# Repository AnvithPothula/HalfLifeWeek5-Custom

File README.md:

# HalfLifeWeek5-Custom

For Week 5 I designed a smart chess clock. It has two OLED screens side by side like a normal chess clock, 5 MX keys, a piezo buzzer, and it runs on 3 AA batteries. After a game, it can connect to Wi-Fi and export the game, with how much time each player had on every move, to a Lichess study.

**3D Model / Final PCB Render:**

**Schematic:**

**Board Layout & Routing:**

Combined Layout:

Front Copper Layer:

Back Copper Layer:

**What it is and how it works:**

Each player has a big key on their side. When you finish your move, you press your key, which stops your clock and starts your opponent's. The 3 keys in the middle are -, Start and +.

The clock has:

- 9 time control presets
- A custom mode where White and Black can have different times
- Increment or delay mode
- A double beep when you drop under 10 seconds, and a long beep when your time runs out
- Tenths of a second on the screen when you have under 20 seconds
- Saving of the last 5 games
- A page where you replay the moves and export the game to a Lichess study
- Deep sleep after 5 minutes of not being used

This is what the screens show during a game (the player whose turn it is gets a highlighted bar at the top):

These are the parts:

* **Waveshare ESP32-S3-Zero:** This is the brain of the board and runs the clocks, saves the games, and connects to Wi-Fi for the export.
* **2 OLED screens:** There is one for each player and shows all of the informaion.
* **4 solder jumpers:** Some of these screens have their pins in the order VCC, GND, SCL, SDA and others have GND, VDD, SCK, SDA. The jumpers let you pick the right order for your screens, so both versions work on the same PCB.
* **5 MX keys:** Each key connects a pin to GND, and the ESP32's pull-up resistors keep the pin HIGH until it's pressed.
* **1N5819 diode:** The 3 AA batteries go through this into the 5V pin. When USB is plugged in, it stops USB power from flowing back into the batteries.
* **2 10k resistors:** These halve the battery voltage so the ESP32 can read the battery level.
* **10uF capacitor:** This smooths out the 5V power.
* **Piezo buzzer:** This makes the beeps.

To export a game, hold Start after the game ends. The clock connects to Wi-Fi and shows its IP address on the left screen. Open that address in a browser on the same Wi-Fi. The page builds the PGN with the clock time for every move, and the clock sends it to the Lichess study.

Note: I used Claude to help write the webpage/exporting part of the code.

**Why I made it:**

I play and coach chess a lot, so a chess clock is something I would actually use. Normal chess clocks don't save anything, so after an over-the-board game, there's no record of how much time each move took. To put it into a chess engine to analyze the game, we would have to notate the game, and then after the game manually enter the moves. With this clock, I can put the game into Lichess and see where I spent too much time. This was also my first project without a guide, where I made the schematic, PCB and firmware all on my own.

**How to assemble and flash the firmware:**

**1. How to assemble the board**

You need a soldering iron, solder, flux, tweezers, flush cutters, a multimeter, and double-sided tape.

First, set the screen jumpers. Look at the back of your screens and check the pin labels. If the screen says VCC GND SCL SDA, bridge the middle pad of JP1 and JP3 to the 3V3 pad, and bridge the middle pad of JP2 and JP4 to the GND pad. If it says GND VDD SCK SDA, do the opposite.

To bridge a jumper, melt a little solder on the middle pad and drag it onto the pad you want.

Then solder from the flattest part to the tallest part:

1. **C1 (10uF capacitor):** Put a little solder on one pad, hold the capacitor with tweezers, and melt that pad to tack it down. Then solder the other end.
2. **R1, R2 (Resistors):** Bend the legs, push them through, solder and trim.
3. **D1 (Diode):** The grey stripe goes on the side with the bar on the silkscreen.
4. **U1 (ESP32-S3-Zero):** Line it up with the outline, with the USB-C port at the top edge. Tack one corner, then solder every edge pad and check for bridges.
5. **SW1–SW5 (MX keys):** Push each key in and then solder its 2 pins.
6. **J1, J2 (screens):** Push each screen's header pins through its 4 holes. Solder one pin, check that the screen is straight, then solder the rest.
7. **Keycaps:** Press them on.

The battery holder and piezo are the only parts with wires. They go on the back of the board:

1. Stick the battery holder to the back with double-sided tape. On J3 (labelled Battery), solder the red wire to the square pad (BAT+) and the black wire to the round pad (GND).
2. Stick the piezo disc to the back with tape or hot glue. Solder its wires to the 2 pads of J4 (labelled Piezo).

Before plugging in, use the multimeter in continuity mode to check that 5V, 3V3 and GND are not shorted, and that each jumper's middle pad only connects to one side.

**2. How to flash the firmware**

1. Install the Arduino IDE.
2. In the Boards Manager, install esp32 by Espressif Systems and select ESP32S3 Dev Module as the board.
3. Under the Tools menu, set USB CDC On Boot to Enabled so the Serial Monitor works over USB-C.
4. Install these libraries in the Library Manager:
   * Adafruit SSD1306
   * Adafruit GFX
   * ArduinoJson
5. Copy ChessClockArduino/secrets_example.h to ChessClockArduino/secrets.h and fill in your Wi-Fi name and password.
6. To export to Lichess, make a token with the study:write scope [here](https://lichess.org/account/oauth/token/create?scopes[]=study:write&description=Chess+Clock) and paste it into LICHESS_TOKEN in secrets.h. Then make a study on Lichess, and put its 8-character ID (from the study's URL) in DEFAULT_STUDY_ID at the top of ChessClockArduino.ino.
7. Open ChessClockArduino/ChessClockArduino.ino, plug the board in with a USB-C data cable, and click Upload. If it doesn't upload, hold the BOOT button on the ESP32-S3-Zero, tap RESET, release BOOT, and try again.

Both screens should show the time. Press Start, and White's clock should start counting down. secrets.h is in .gitignore, so your Wi-Fi password and token won't be uploaded to GitHub.

**BOM:**

The full bill of materials is in [BOM.csv](BOM.csv):

| Item | Qty | Supplier | Cost/item | Total cost | Link |
| --- | ---: | --- | ---: | ---: | --- |
| ESP32-S3-Zero (no headers) | 1 | AliExpress | $4.32 | $4.32 | [AliExpress](https://www.aliexpress.us/item/3256807949476561.html) |
| 0.96" OLED 128x64 I2C (SSD1306, white 2-pack) | 1 | AliExpress | $4.40 | $4.40 | [AliExpress](https://www.aliexpress.us/item/3256805954920554.html) |
| 27mm piezo with wires (10-pack) | 1 | AliExpress | $4.70 | $4.70 | [AliExpress](https://www.aliexpress.us/item/3256806921009045.html) |
| 3x AA battery holder with switch | 1 | AliExpress | $1.44 | $1.44 | [AliExpress](https://www.aliexpress.us/item/2255800794307346.html) |
| 1N5819 Schottky diode (50-pack) | 1 | AliExpress | $1.32 | $1.32 | [AliExpress](https://www.aliexpress.us/item/3256801365779334.html) |
| MX switches (10-pack, red) | 1 | AliExpress | $1.88 | $1.88 | [AliExpress](https://www.aliexpress.us/item/3256807066857216.html) |
| Keycaps (10-pack, red) | 1 | AliExpress | $2.32 | $2.32 | [AliExpress](https://www.aliexpress.us/item/3256807312571573.html) |
| 10k resistors (spare from Week 4) | 2 | — | $0.00 | $0.00 | — |
| 10uF 0805 capacitor (spare from Week 4) | 1 | — | $0.00 | $0.00 | — |
| PCB | 1 | JLCPCB | $4.00 | $4.00 | [JLCPCB](https://jlcpcb.com/) |
| Shipping (AliExpress Choice) | — | AliExpress | — | $0.00 | — |
| Shipping (JLCPCB Global Standard Direct Line) | — | JLCPCB | — | $3.78 (-$5 coupon) | — |
| Estimated sales tax (8.125% on AliExpress parts) | — | — | — | $1.66 | — |
| **Estimated total** |  |  |  | **$29.82** |  |

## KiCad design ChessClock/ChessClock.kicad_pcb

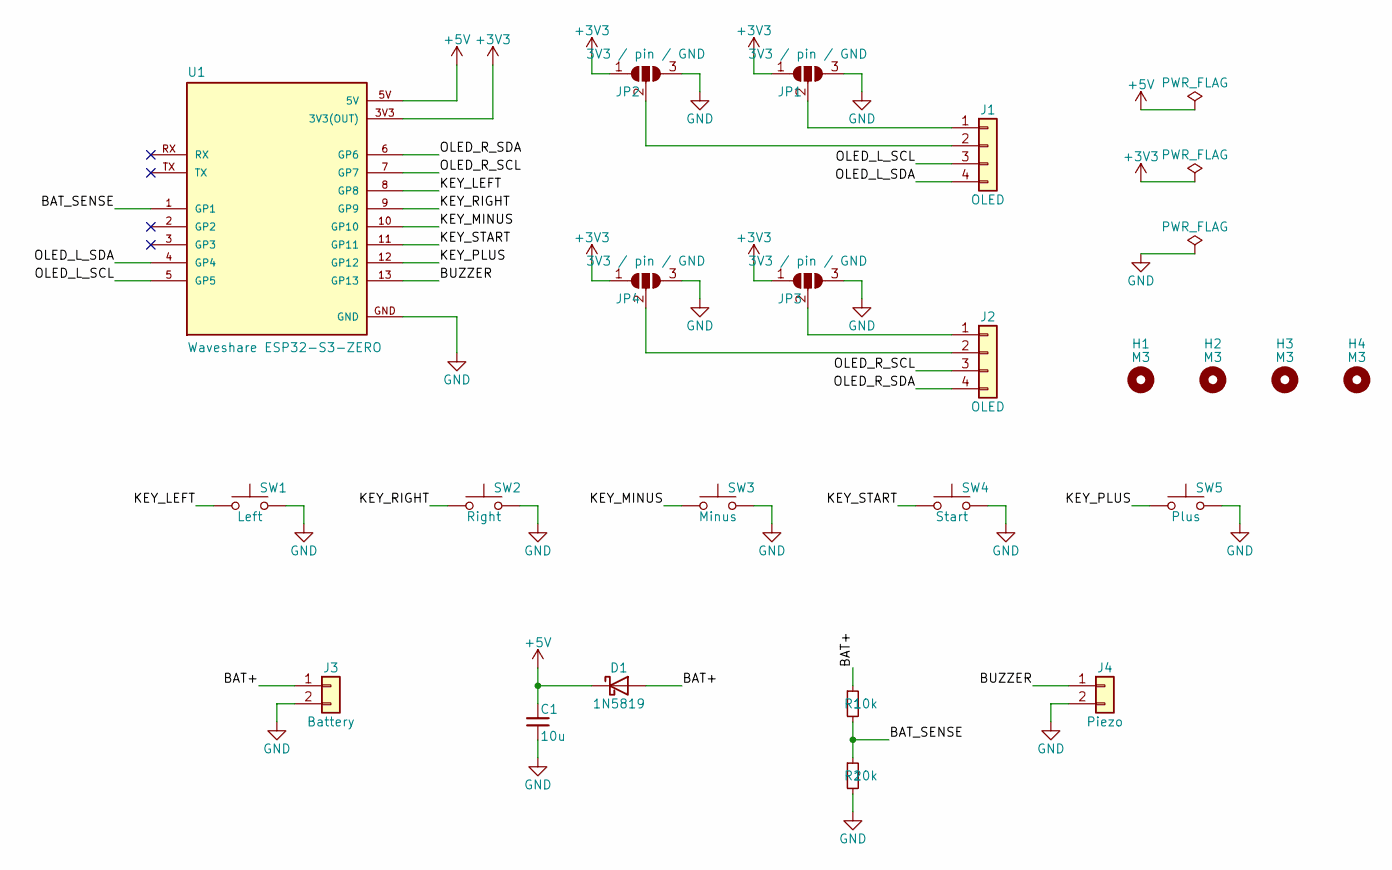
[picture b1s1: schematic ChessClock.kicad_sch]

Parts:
C1: 10u; C_0805_2012Metric
D1: 1N5819; D_DO-41_SOD81_P10.16mm_Horizontal
H1, H2, H3, H4: M3; MountingHole_3.2mm_M3
J1, J2: OLED; PinHeader_1x04_P2.54mm_Vertical
J3: Battery; SolderWire-0.25sqmm_1x02_P4.2mm_D0.65mm_OD1.7mm
J4: Piezo; SolderWire-0.25sqmm_1x02_P4.2mm_D0.65mm_OD1.7mm
JP1, JP2, JP3, JP4: 3V3 / pin / GND; SolderJumper-3_P1.3mm_Open_RoundedPad1.0x1.5mm
R1, R2: 10k; R_Axial_DIN0207_L6.3mm_D2.5mm_P10.16mm_Horizontal
SW1: Left; SW_Cherry_MX_1.00u_PCB
SW2: Right; SW_Cherry_MX_1.00u_PCB
SW3: Minus; SW_Cherry_MX_1.00u_PCB
SW4: Start; SW_Cherry_MX_1.00u_PCB
SW5: Plus; SW_Cherry_MX_1.00u_PCB
U1: Waveshare ESP32-S3-ZERO; Waveshare ESP32-S3-Zero; PARTREV NA

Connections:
+3V3: JP1.1 (A), JP2.1 (A), JP3.1 (A), JP4.1 (A), U1.3V3 (3V3(OUT))
+5V: C1.1, D1.1 (K), U1.5V
/BAT+: D1.2 (A), J3.1, R1.1
/BAT_SENSE: R1.2, R2.1, U1.1 (GP1)
/BUZZER: J4.1, U1.13 (GP13)
/KEY_LEFT: SW1.1, U1.8 (GP8)
/KEY_MINUS: SW3.1, U1.10 (GP10)
/KEY_PLUS: SW5.1, U1.12 (GP12)
/KEY_RIGHT: SW2.1, U1.9 (GP9)
/KEY_START: SW4.1, U1.11 (GP11)
/OLED_L_SCL: J1.3, U1.5 (GP5)
/OLED_L_SDA: J1.4, U1.4 (GP4)
/OLED_R_SCL: J2.3, U1.7 (GP7)
/OLED_R_SDA: J2.4, U1.6 (GP6)
GND: C1.2, J3.2, J4.2, JP1.3 (B), JP2.3 (B), JP3.3 (B), JP4.3 (B), R2.2, SW1.2, SW2.2, SW3.2, SW4.2, SW5.2, U1.GND
unnamed: J1.1, JP1.2 (C)
unnamed: J1.2, JP2.2 (C)
unnamed: J2.1, JP3.2 (C)
unnamed: J2.2, JP4.2 (C)

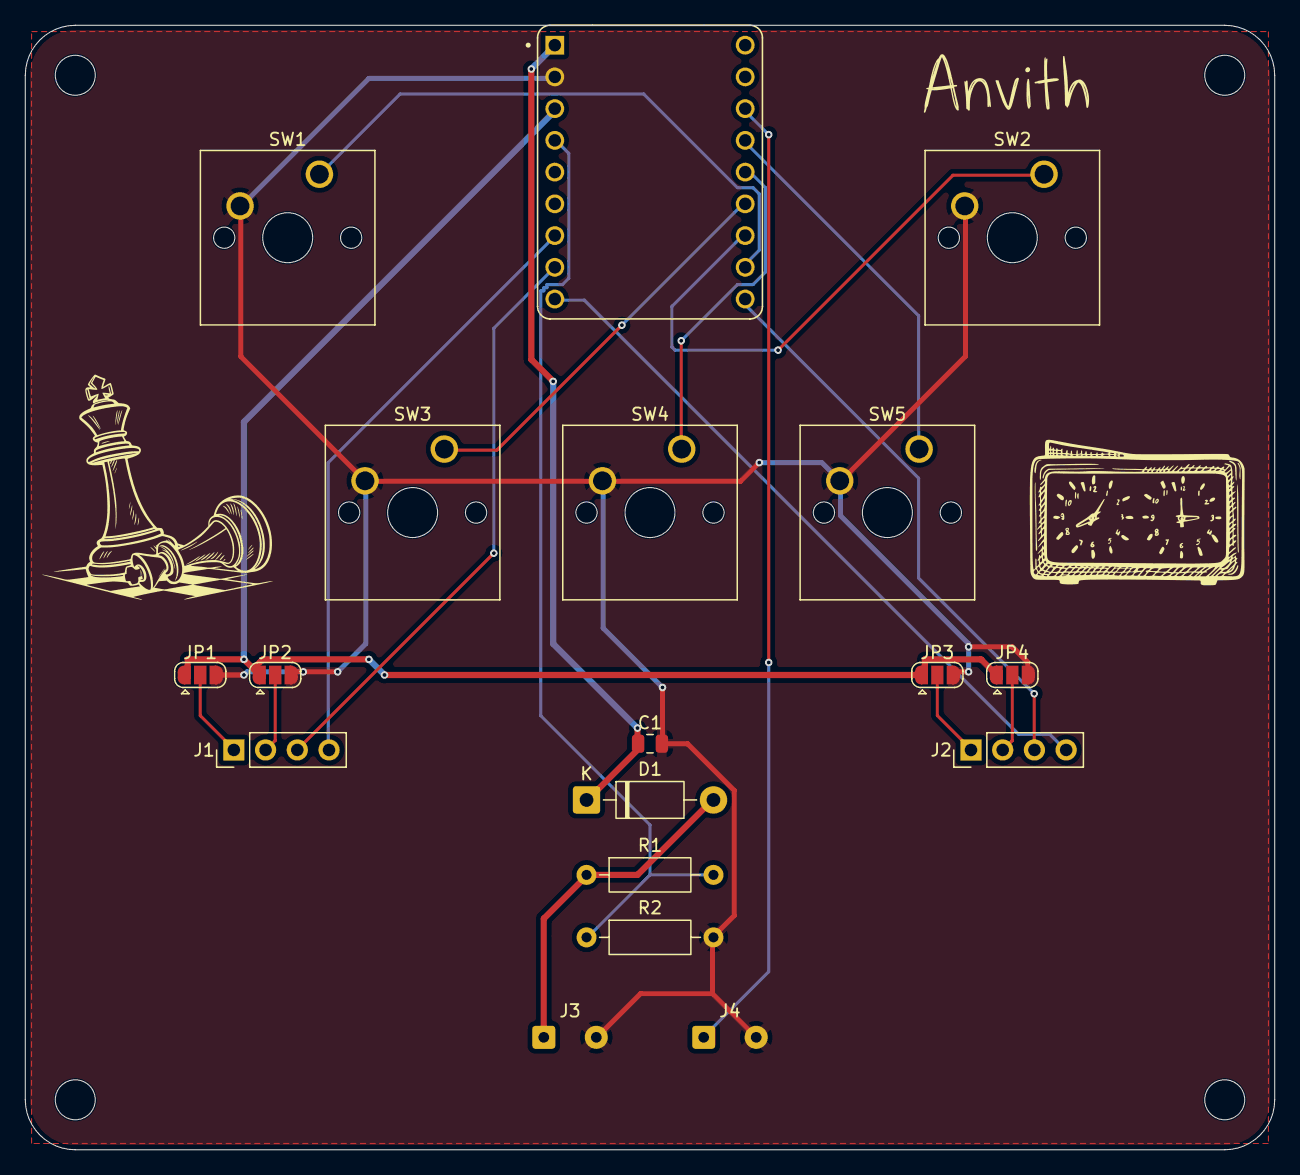
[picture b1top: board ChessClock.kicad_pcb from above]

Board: 2 copper layers, 100.0 x 90.0 mm, 22 parts (0 on the bottom side), 19 nets.

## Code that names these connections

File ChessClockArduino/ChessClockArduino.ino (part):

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
// pins
#define PIN_BATTERY 1
#define PIN_OLED_L_SDA 4
#define PIN_OLED_L_SCL 5
#define PIN_OLED_R_SDA 6
#define PIN_OLED_R_SCL 7
#define PIN_KEY_LEFT 8
#define PIN_KEY_RIGHT 9
#define PIN_KEY_MINUS 10
#define PIN_KEY_START 11
#define PIN_KEY_PLUS 12
#define PIN_BUZZER 13

// screens
const uint8_t OLED_ADDRESS = 0x3C;
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};

// keys
const uint8_t PLAYER_KEY_PINS[2] = {PIN_KEY_LEFT, PIN_KEY_RIGHT};
const unsigned long KEY_SETTLE_MS = 30;
volatile bool playerKeyHeld[2] = {false, false};
volatile unsigned long playerKeyReleasedAt[2] = {0, 0};
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const unsigned long REPEAT_DELAY_MS = 450;
const unsigned long REPEAT_RATE_MS = 120;

Button keyMinus = {PIN_KEY_MINUS};
Button keyStart = {PIN_KEY_START};
Button keyPlus = {PIN_KEY_PLUS};

void initButton(Button& b) {
  pinMode(b.pin, INPUT_PULLUP);
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  if (beepsLeft == 0 && !beepOn) return;
  if ((long)(now - beepNextAt) < 0) return;
  if (beepOn) {
    ledcWriteTone(PIN_BUZZER, 0);
    beepOn = false;
    beepNextAt = now + beepOffMs;
  } else if (beepsLeft > 0) {
    ledcWriteTone(PIN_BUZZER, beepFreq);
    beepOn = true;
    beepsLeft--;
    beepNextAt = now + beepOnMs;
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// sleep
void goToSleep() {
  saveSettings();
  ledcWriteTone(PIN_BUZZER, 0);
  oledLeft.ssd1306_command(SSD1306_DISPLAYOFF);
  oledRight.ssd1306_command(SSD1306_DISPLAYOFF);

  const uint8_t wakePins[3] = {PIN_KEY_LEFT, PIN_KEY_RIGHT, PIN_KEY_START};
  uint64_t mask = 0;
  for (int i = 0; i < 3; i++) {
    gpio_num_t pin = (gpio_num_t)wakePins[i];
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  Serial.begin(115200);

  if (esp_sleep_get_wakeup_cause() == ESP_SLEEP_WAKEUP_EXT1) {
    rtc_gpio_deinit((gpio_num_t)PIN_KEY_LEFT);
    rtc_gpio_deinit((gpio_num_t)PIN_KEY_RIGHT);
    rtc_gpio_deinit((gpio_num_t)PIN_KEY_START);
  }

  initButton(keyMinus);
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    pinMode(PLAYER_KEY_PINS[side], INPUT_PULLUP);
    playerKeyHeld[side] = digitalRead(PLAYER_KEY_PINS[side]) == LOW;
  }
  attachInterrupt(digitalPinToInterrupt(PIN_KEY_LEFT), onLeftKeyChange, CHANGE);
  attachInterrupt(digitalPinToInterrupt(PIN_KEY_RIGHT), onRightKeyChange, CHANGE);

  ledcAttach(PIN_BUZZER, 2000, 8);
  ledcWriteTone(PIN_BUZZER, 0);
  analogSetPinAttenuation(PIN_BATTERY, ADC_11db);

  Wire.begin(PIN_OLED_L_SDA, PIN_OLED_L_SCL, 400000);
  Wire1.begin(PIN_OLED_R_SDA, PIN_OLED_R_SCL, 400000);
  bool leftOk = oledLeft.begin(SSD1306_SWITCHCAPVCC, OLED_ADDRESS, true, false);
  bool rightOk = oledRight.begin(SSD1306_SWITCHCAPVCC, OLED_ADDRESS, true, false);
  if (!leftOk) Serial.println("Left OLED not found - check its wiring");
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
